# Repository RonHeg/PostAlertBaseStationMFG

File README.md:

# PostAlertBaseStationMFG
 PostAlert IoT Base station Documentation for manufacturing

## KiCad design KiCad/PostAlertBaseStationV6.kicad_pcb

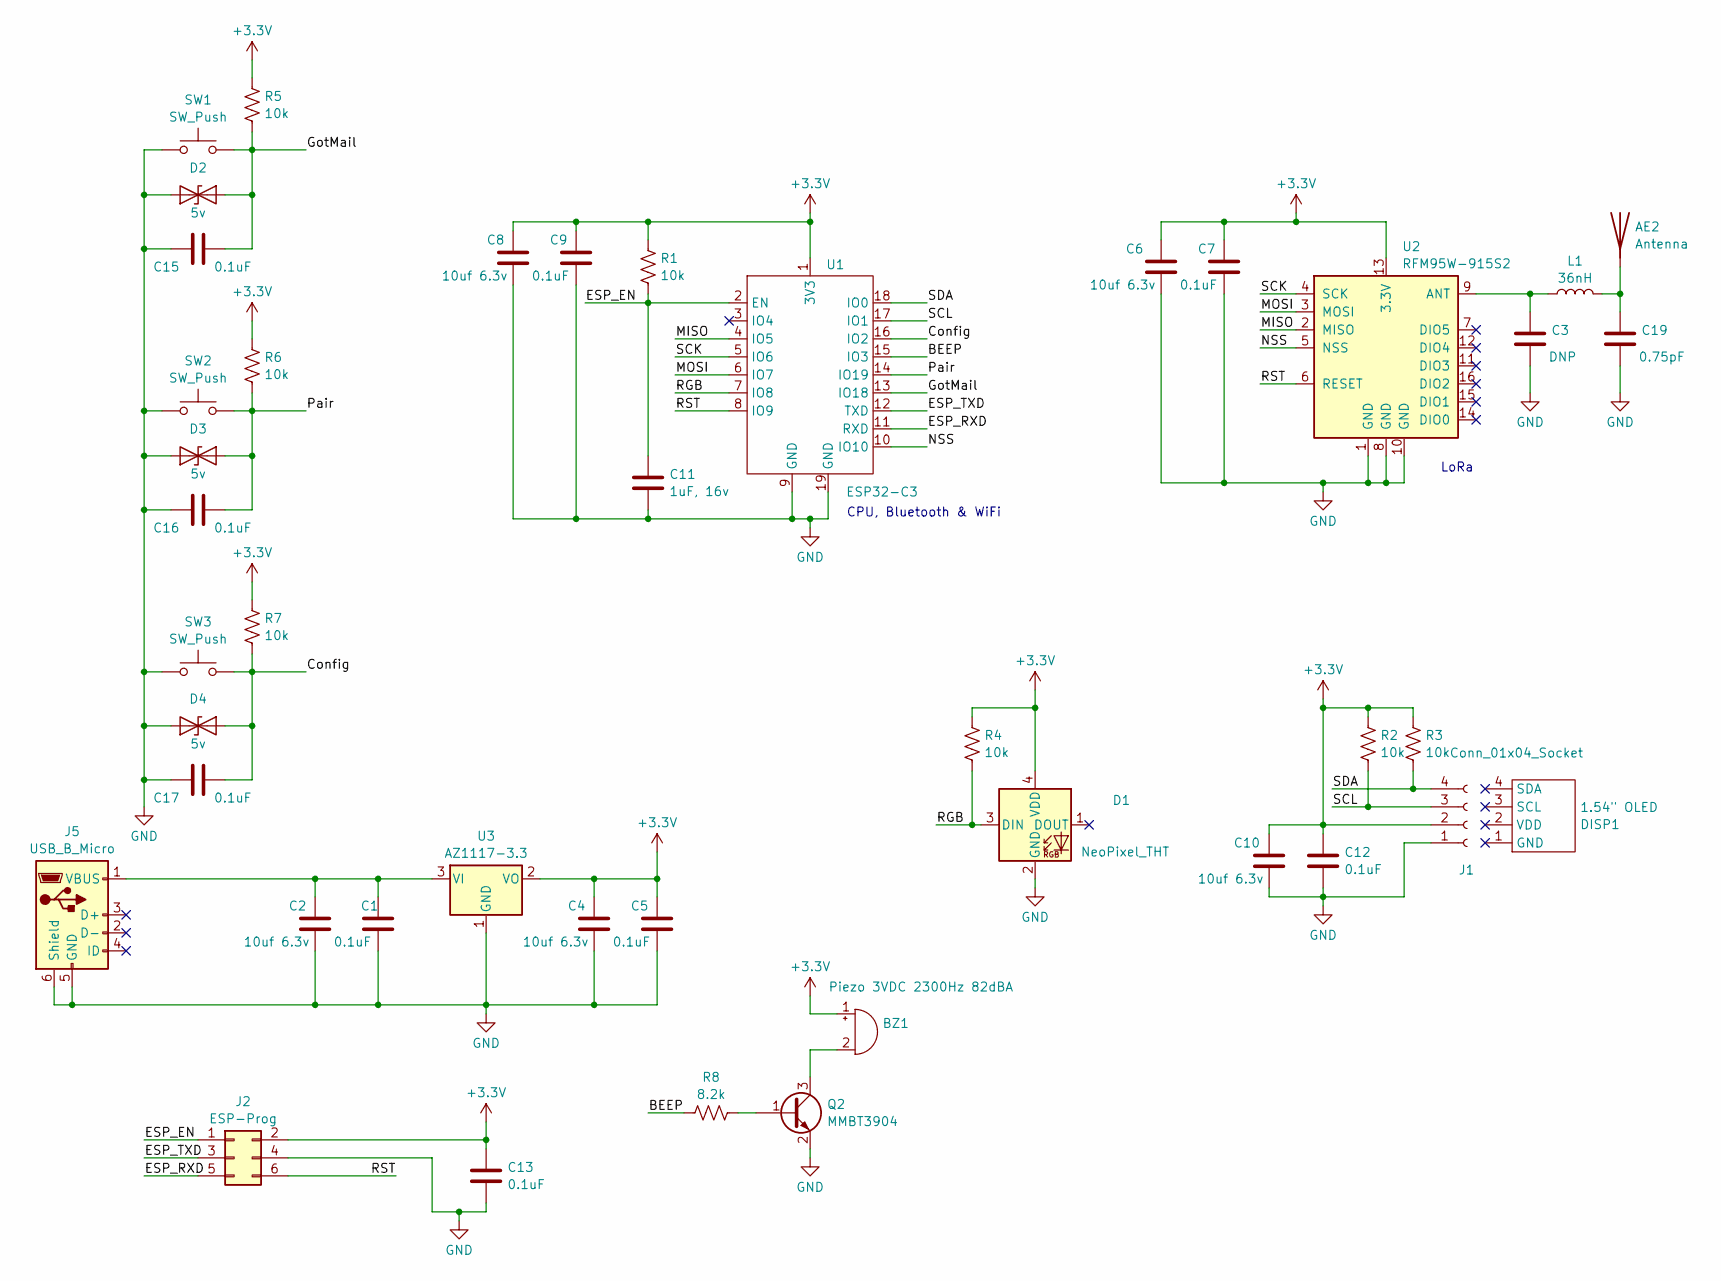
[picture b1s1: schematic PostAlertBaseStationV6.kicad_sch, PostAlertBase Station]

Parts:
AE2: Antenna; Texas_SWRA416_868MHz_915MHz
BZ1: Piezo 3VDC 2300Hz 82dBA; Buzzer_15x7.5RM7.6
C1, C5, C7, C9, C12, C13, C15, C16, C17: 0.1uF; C_0603_1608Metric
C2, C4, C6, C8, C10: 10uf 6.3v; C_0805_2012Metric
C3: DNP; C_0603_1608Metric
C11: 1uF, 16v; C_0603_1608Metric
C19: 0.75pF; C_0603_1608Metric
D1: NeoPixel_THT; LED_WS2812B-2020_PLCC4_2.0x2.0mm
D2, D3, D4: 5v; D_0603_1608Metric
DISP1: 1.54" OLED; DISPLAY-OLED-1.54_IIC_1
J1: Conn_01x04_Socket; PinSocket_1x04_P2.54mm_Vertical
J2: ESP-Prog; PinHeader_2x03_P1.27mm_Vertical_SMD
J5: USB_B_Micro; USB_Micro-B_Amphenol_10118193-0002LF_Horizontal
L1: 36nH; L_0603_1608Metric
Q2: MMBT3904; SOT-23
R1, R2, R3, R4, R5, R6, R7: 10k; R_0603_1608Metric
R8: 8.2k; R_0603_1608Metric
SW1: SW_Push; SW_PUSH_6mm
SW2, SW3: SW_Push; SW_Tactile_SKHH_Angled
U1: ESP32-C3; ESP-WROOM-02
U2: RFM95W-915S2; HOPERF_RFM9XW_SMD
U3: AZ1117-3.3; SOT-223-3_TabPin2

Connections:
+3.3V: BZ1.1 (+), C4.1, C5.1, C6.1, C7.1, C8.1, C9.1, C10.1, C12.1, C13.1, D1.4 (VDD), J1.2, J2.2, R1.1, R2.1, R3.1, R4.1, R5.1, R6.1, R7.1, U1.1 (3V3), U2.13 (3.3V), U3.2 (VO)
/BEEP: R8.1, U1.15 (IO3)
/Config: C17.2, D4.1 (A1), R7.2, SW3.2, U1.16 (IO2)
/ESP_EN: C11.1, J2.1, R1.2, U1.2 (EN)
/ESP_RXD: J2.5, U1.11 (RXD)
/ESP_TXD: J2.3, U1.12 (TXD)
/GotMail: C15.2, D2.1 (A1), R5.2, SW1.2, U1.13 (IO18)
/MISO: U1.4 (IO5), U2.2 (MISO)
/MOSI: U1.6 (IO7), U2.3 (MOSI)
/NSS: U1.10 (IO10), U2.5 (NSS)
/Pair: C16.2, D3.1 (A1), R6.2, SW2.1, U1.14 (IO19)
/RGB: D1.3 (DIN), R4.2, U1.7 (IO8)
/RST: J2.6, U1.8 (IO9), U2.6 (RESET)
/SCK: U1.5 (IO6), U2.4 (SCK)
/SCL: J1.3, R2.2, U1.17 (IO1)
/SDA: J1.4, R3.2, U1.18 (IO0)
GND: C1.2, C2.2, C3.2, C4.2, C5.2, C6.2, C7.2, C8.2, C9.2, C10.2, C11.2, C12.2, C13.2, C15.1, C16.1, C17.1, C19.2, D1.2 (GND), D2.2 (A2), D3.2 (A2), D4.2 (A2), J1.1, J2.4, J5.5 (GND), J5.6 (Shield), Q2.2 (E), SW1.1, SW2.2, SW3.1, U1.9 (GND), U1.19 (GND), U2.1 (GND), U2.8 (GND), U2.10 (GND), U3.1 (GND)
unnamed: AE2.1 (A), C19.1, L1.2
unnamed: BZ1.2 (-), Q2.3 (C)
unnamed: C1.1, C2.1, J5.1 (VBUS), U3.3 (VI)
unnamed: Q2.1 (B), R8.2
unnamed: C3.1, L1.1, U2.9 (ANT)

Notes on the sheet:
CPU, Bluetooth & WiFi
LoRa

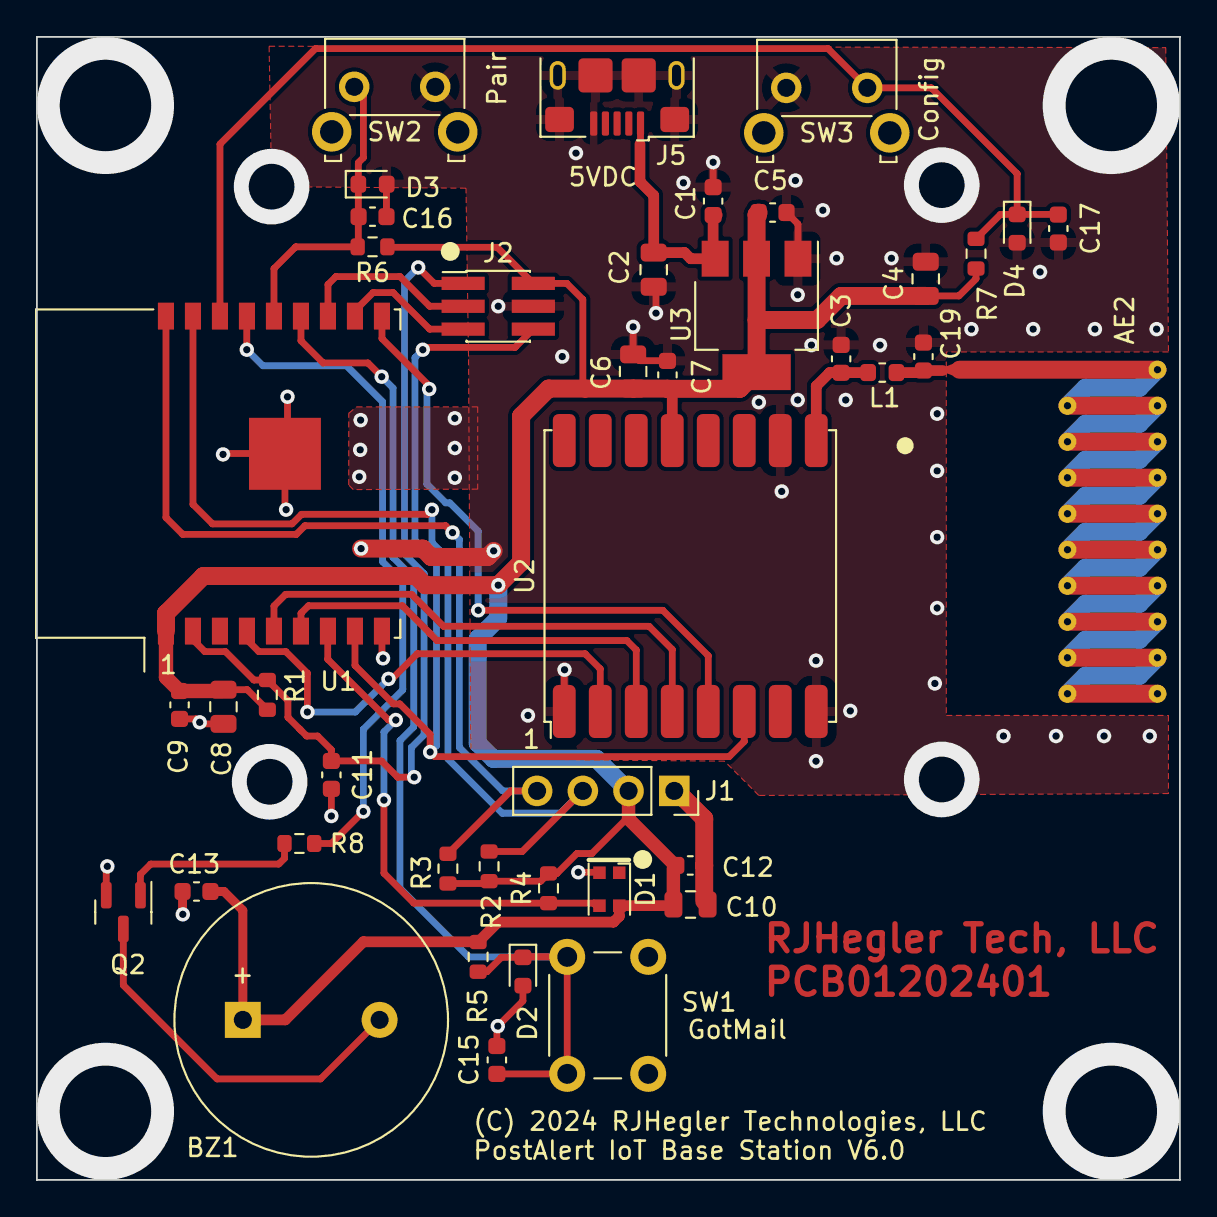
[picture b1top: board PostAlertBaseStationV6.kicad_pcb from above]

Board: 2 copper layers, 63.5 x 63.5 mm, 42 parts (0 on the bottom side), 22 nets.

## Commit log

2025-02-27 Initial file transfer
    Files required to manufacture the PostAlert IoI as of 2/27/2025
2025-02-27 Update README.md
    fixed caps lock text
2025-02-27 Add front panel overlay
    Front panel drawings were missing
2025-03-01 Add initial test report
    Report shows EMI scans

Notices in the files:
KiCad/PostAlertBaseStationV6.kicad_pcb:
(C) 2024 RJHegler Technologies, LLC
